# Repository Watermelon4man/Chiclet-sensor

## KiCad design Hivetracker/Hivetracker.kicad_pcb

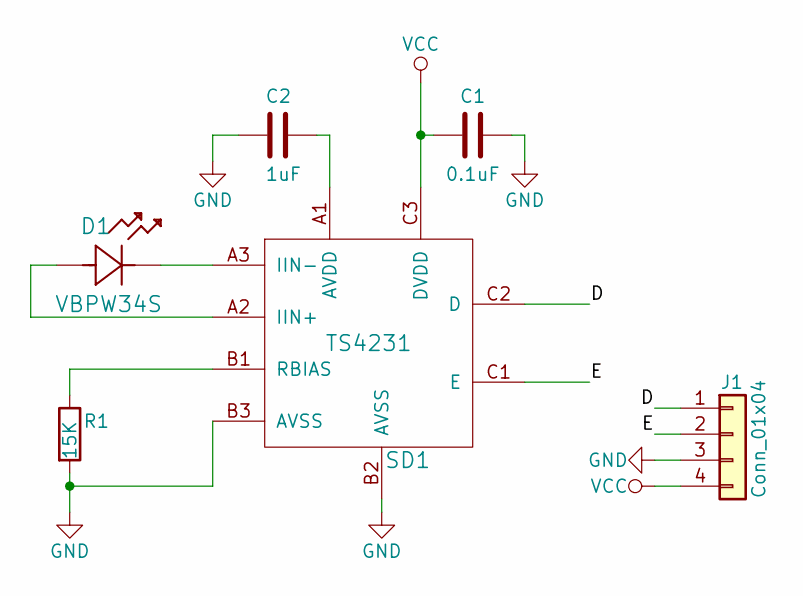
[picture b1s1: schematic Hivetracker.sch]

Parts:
C1: 0.1uF; C_0402_1005Metric
C2: 1uF; C_0402_1005Metric
D1: VBPW34S
J1: Conn_01x04; PinHeader_1x04_P1.00mm_Vertical
R1: 15K; R_0402_1005Metric
SD1: TS4231

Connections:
/D: J1.1, SD1.C2 (D)
/E: J1.2, SD1.C1 (E)
GND: C1.1, C2.2, J1.3, R1.2, SD1.B2 (AVSS), SD1.B3 (AVSS)
unnamed: C2.1, SD1.A1 (AVDD)
unnamed: D1.1, SD1.A3 (IIN-)
unnamed: D1.2, SD1.A2 (IIN+)
unnamed: R1.1, SD1.B1 (RBIAS)
VCC: C1.2, J1.4, SD1.C3 (DVDD)

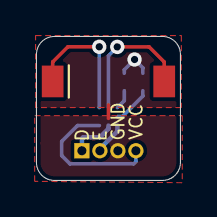
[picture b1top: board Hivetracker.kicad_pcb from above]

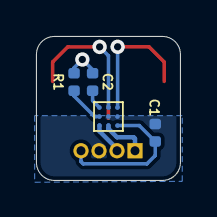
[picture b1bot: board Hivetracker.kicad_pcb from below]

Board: 2 copper layers, 8.0 x 8.0 mm, 6 parts (4 on the bottom side), 8 nets.

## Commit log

2021-07-20 added files
2021-07-20 added gerber
